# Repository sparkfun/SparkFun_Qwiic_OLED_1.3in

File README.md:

SparkFun Qwiic OLED 1.3in (128 x 64 white pixels)
========================================

[*Qwiic OLED 1.3in (128 x 64 white pixels) (LCD-23453)*](https://www.sparkfun.com/products/23453)

The SparkFun Qwiic OLED 1.3in (128 x 64 white pixels) Breakout is a Qwiic-enabled OLED display.

Repository Contents
-------------------

* **/Hardware** - Eagle design files (.brd, .sch)

Documentation
--------------
* **[Library](https://github.com/sparkfun/SparkFun_Qwiic_OLED_Arduino_Library)** - Latest Arduino library for the SparkFun Qwiic OLED 1.3in Breakout.
* **[Hookup Guide](https://docs.sparkfun.com/SparkFun_Qwiic_OLED_1.3in)** - Basic hookup guide for the SparkFun Qwiic OLED 1.3in

License Information
-------------------

This product is _**open source**_! 

Please review the LICENSE.md file for license information. 

If you have any questions or concerns on licensing, please contact techsupport@sparkfun.com.

Distributed as-is; no warranty is given.

- Your friends at SparkFun.

_<COLLABORATION CREDIT>_

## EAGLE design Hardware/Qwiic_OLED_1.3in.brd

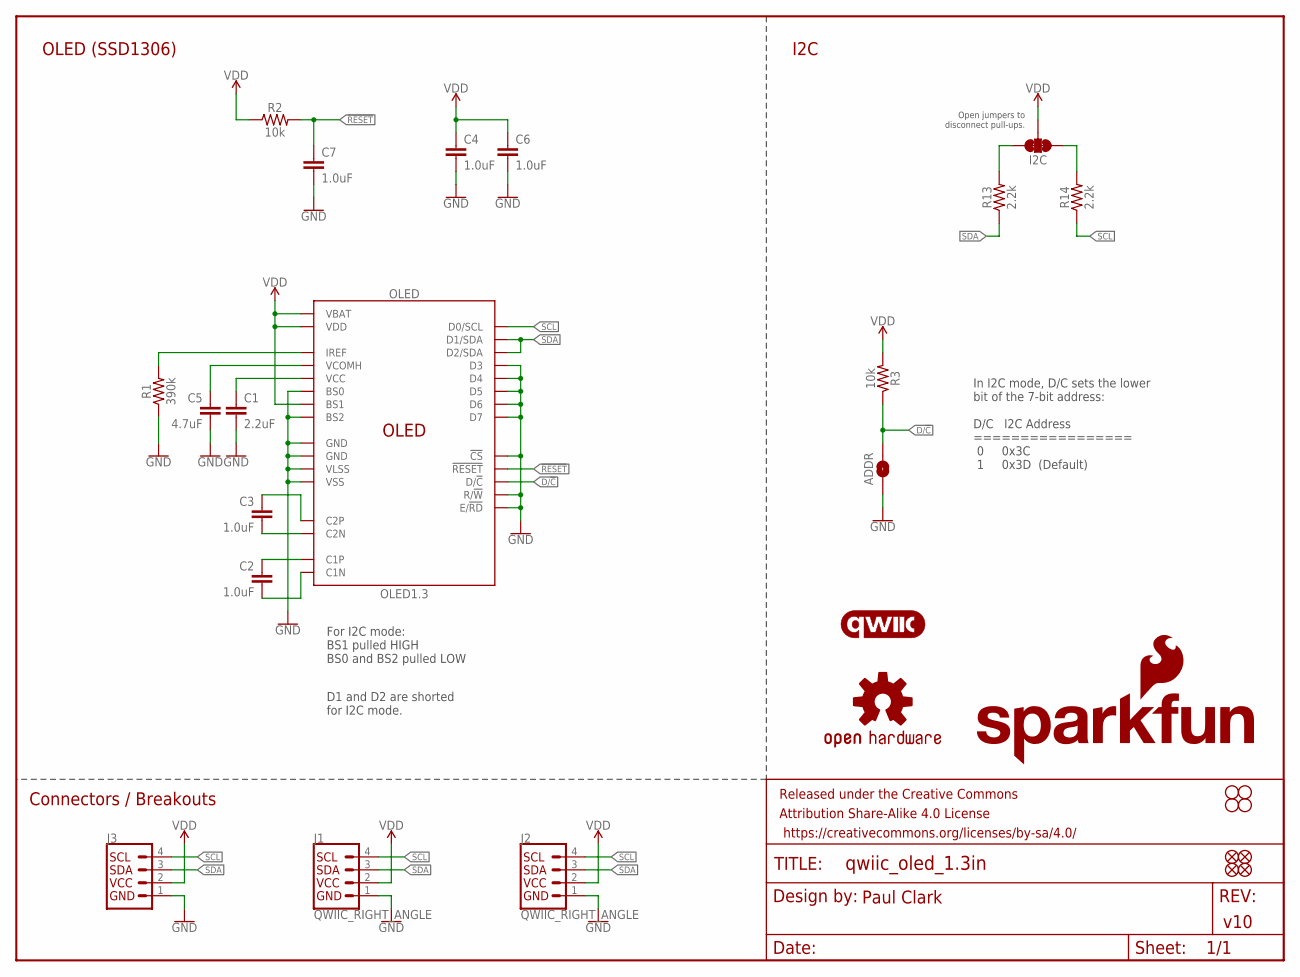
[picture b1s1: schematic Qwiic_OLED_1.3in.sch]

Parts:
ADDR: JUMPER-SMT_2_NO_SILK; SMT-JUMPER_2_NO_SILK
C1: 2.2uF; 0603
C2, C3, C4, C6, C7: 1.0uF; 0603
C5: 4.7uF; 0603
FID1, FID2, FID3, FID4: FIDUCIAL1X2; FIDUCIAL-1X2
FRAME1: FRAME-LETTER; CREATIVE_COMMONS
H1, H2, H3, H4: STAND-OFF
I2C: JUMPER-SMT_3_2-NC_TRACE_SILK; SMT-JUMPER_3_2-NC_TRACE_SILK
J1, J2: QWIIC_RIGHT_ANGLE; JST04_1MM_RA
J3: I2C_STANDARD_NO_SILK; 1X04_NO_SILK
LOGO1: QWIIC_LOGO_6MM; QWIIC_6MM
LOGO3: OSHW-LOGOS; OSHW-LOGO-S
LOGO4: SFE_LOGO_NAME_FLAME.1_INCH; SFE_LOGO_NAME_FLAME_.1
OLED: OLED1.3; OLED-1.3-128X64
R1: 390k; 0603
R2, R3: 10k; 0603
R13, R14: 2.2k; 0603

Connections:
!RESET!: C7.1, OLED.14 (!RESET!), R2.2
C1N: C2.2, OLED.5 (C1N)
C1P: C2.1, OLED.4 (C1P)
C2N: C3.2, OLED.3 (C2N)
C2P: C3.1, OLED.2 (C2P)
D/!C!: ADDR.2, OLED.15 (D/!C!), R3.1
GND: ADDR.1, C1.2, C4.2, C5.2, C6.2, C7.2, J1.1, J2.1, J3.1 (GND), OLED.1 (GND), OLED.8 (VSS), OLED.10 (BS0), OLED.12 (BS2), OLED.13 (!CS!), OLED.16 (R/!W!), OLED.17 (E/!RD!), OLED.21 (D3), OLED.22 (D4), OLED.23 (D5), OLED.24 (D6), OLED.25 (D7), OLED.29 (VLSS), OLED.30 (GND), R1.1
IREF: OLED.26 (IREF), R1.2
unnamed: I2C.3, R13.2
unnamed: I2C.1, R14.2
SCL: J1.4, J2.4, J3.4 (SCL), OLED.18 (D0/SCL), R14.1
SDA: J1.3, J2.3, J3.3 (SDA), OLED.19 (D1/SDA), OLED.20 (D2/SDA), R13.1
VCC: C1.1, OLED.28 (VCC)
VCOMH: C5.1, OLED.27 (VCOMH)
VDD: C4.1, C6.1, I2C.2, J1.2, J2.2, J3.2 (VCC), OLED.6 (VBAT), OLED.9 (VDD), OLED.11 (BS1), R2.1, R3.2

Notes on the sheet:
v10
D1 and D2 are shorted for I2C mode.
In I2C mode, D/C sets the lower bit of the 7-bit address: D/C I2C Address ================= 0 0x3C 1 0x3D (Default)
For I2C mode: BS1 pulled HIGH BS0 and BS2 pulled LOW
Open jumpers to disconnect pull-ups.
Paul Clark
OLED (SSD1306)
Connectors / Breakouts
I2C

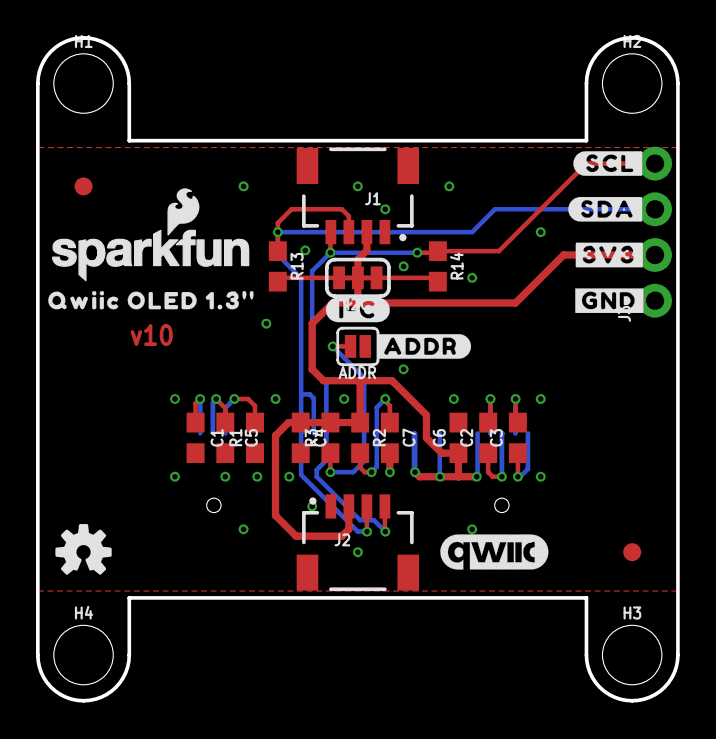
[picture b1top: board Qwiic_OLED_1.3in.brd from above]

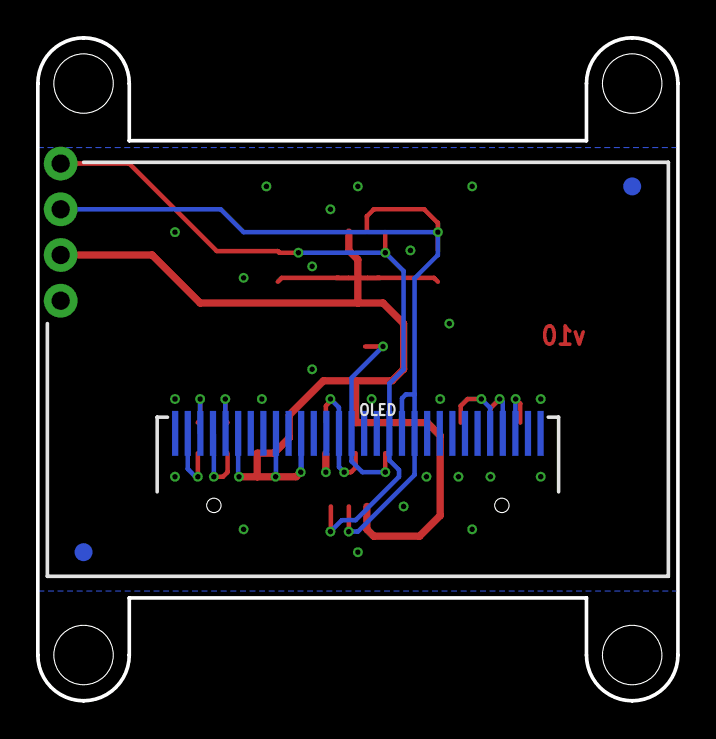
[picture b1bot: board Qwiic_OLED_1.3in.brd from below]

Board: 2 copper layers, 35.6 x 36.8 mm, 37 parts (3 on the bottom side), 15 nets.

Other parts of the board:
U$1: QWIIC_OLED_1#3##0
U$2: #I�C#2
U$3: #3V3#2
U$4: #ADDR#5
U$5: #GND#4
U$6: #SCL#0
U$7: #SDA#1

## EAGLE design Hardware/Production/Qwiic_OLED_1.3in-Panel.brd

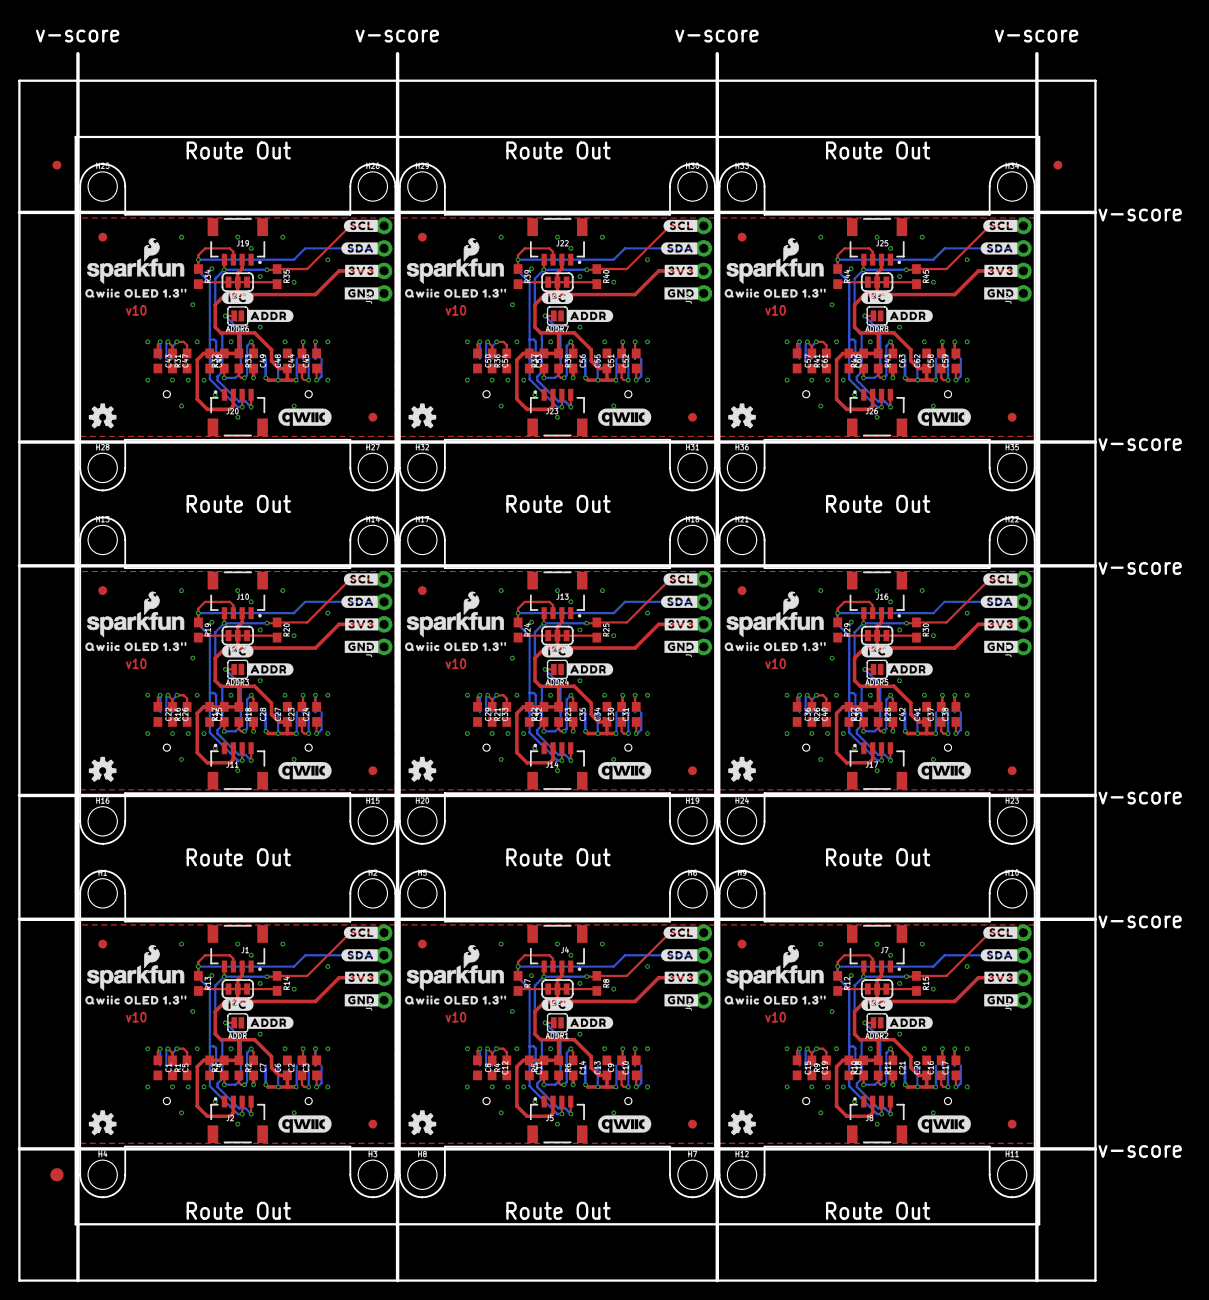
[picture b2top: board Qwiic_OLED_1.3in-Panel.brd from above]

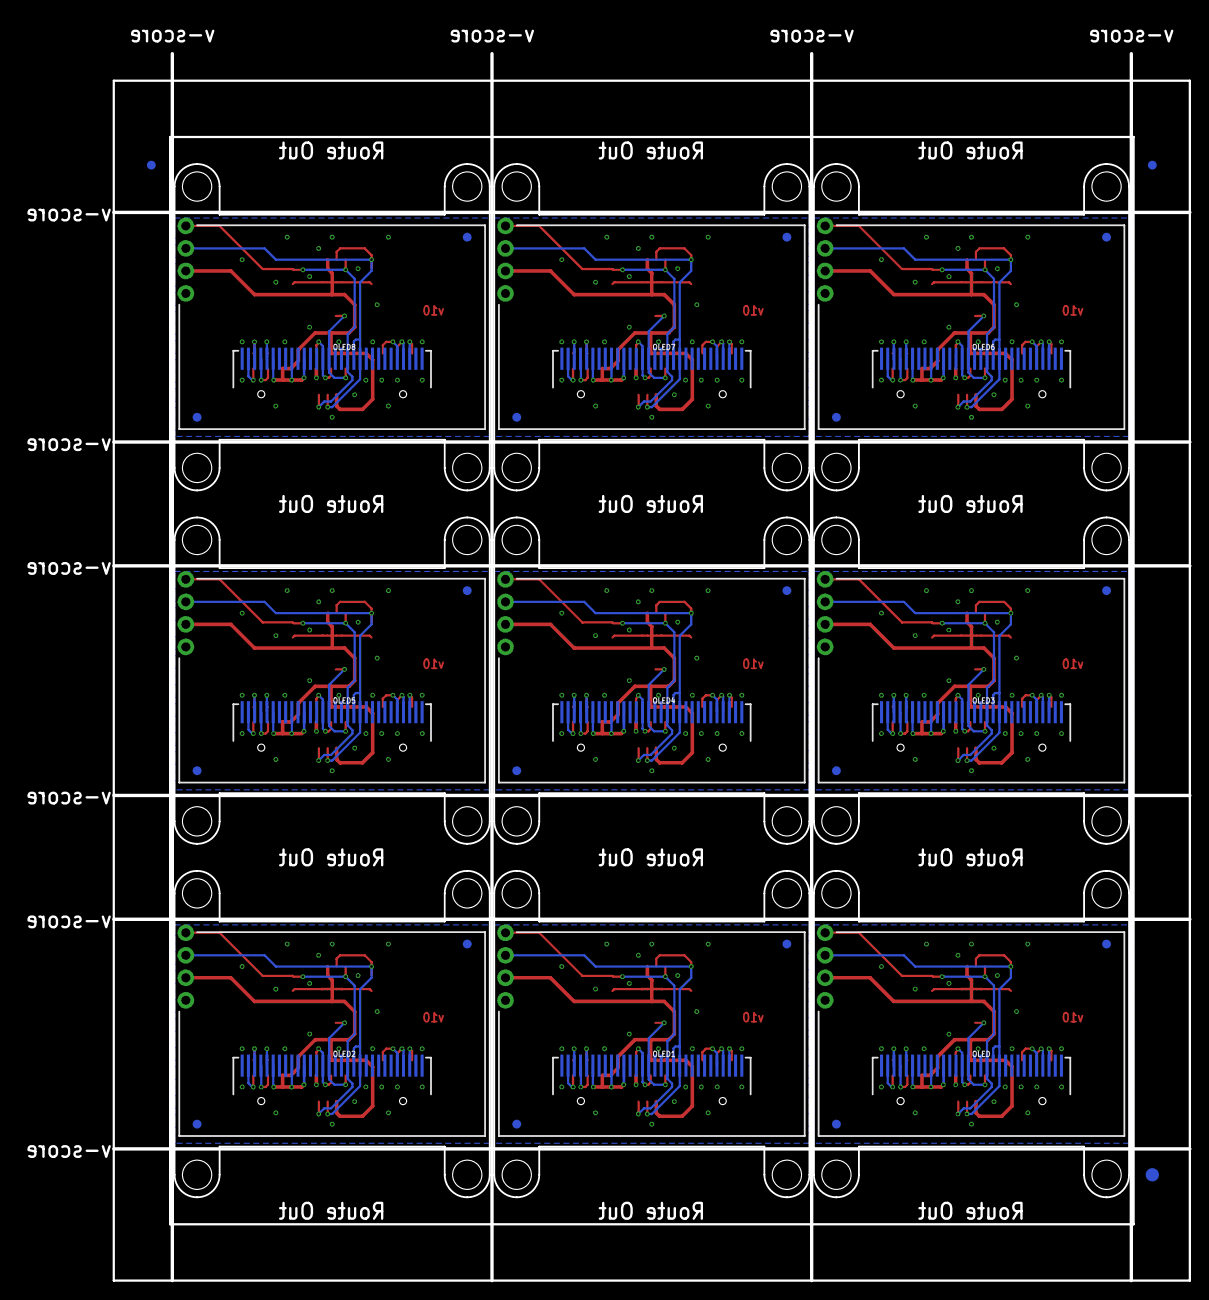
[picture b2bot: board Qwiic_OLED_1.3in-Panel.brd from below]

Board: 2 copper layers, 132.1 x 142.3 mm, 330 parts (30 on the bottom side), 135 nets.

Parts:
ADDR, ADDR1, ADDR2, ADDR3, ADDR4, ADDR5, ADDR6, ADDR7, ADDR8: JUMPER-SMT_2_NO_SILK; SMT-JUMPER_2_NO_SILK
C1, C8, C15, C22, C29, C36, C43, C50, C57: 2.2uF; 0603
C2, C3, C4, C6, C7, C9, C10, C11, C13, C14, C16, C17, C18, C20, C21, C23, C24, C25, C27, C28, C30, C31, C32, C34, C35, C37, C38, C39, C41, C42, C44, C45, C46, C48, C49, C51, C52, C53, C55, C56, C58, C59, C60, C62, C63: 1.0uF; 0603
C5, C12, C19, C26, C33, C40, C47, C54, C61: 4.7uF; 0603
E$1, E$2, E$3, E$4: FIDUCIAL-1X2
E$5, E$6: FIDUCIAL-1.5X3
FID1, FID2, FID3, FID4, FID5, FID6, FID7, FID8, FID9, FID10, FID11, FID12, FID13, FID14, FID15, FID16, FID17, FID18, FID19, FID20, FID21, FID22, FID23, FID24, FID25, FID26, FID27, FID28, FID29, FID30, FID31, FID32, FID33, FID34, FID35, FID36: FIDUCIAL1X2; FIDUCIAL-1X2
H1, H2, H3, H4, H5, H6, H7, H8, H9, H10, H11, H12, H13, H14, H15, H16, H17, H18, H19, H20, H21, H22, H23, H24, H25, H26, H27, H28, H29, H30, H31, H32, H33, H34, H35, H36: STAND-OFF
I2C, I2C1, I2C2, I2C3, I2C4, I2C5, I2C6, I2C7, I2C8: JUMPER-SMT_3_2-NC_TRACE_SILK; SMT-JUMPER_3_2-NC_TRACE_SILK
J1, J2, J4, J5, J7, J8, J10, J11, J13, J14, J16, J17, J19, J20, J22, J23, J25, J26: QWIIC_RIGHT_ANGLE; JST04_1MM_RA
J3, J6, J9, J12, J15, J18, J21, J24, J27: 1X04_NO_SILK
LOGO1, LOGO6, LOGO9, LOGO12, LOGO15, LOGO18, LOGO21, LOGO24, LOGO27: QWIIC_LOGO_6MM; QWIIC_6MM
LOGO2, LOGO3, LOGO7, LOGO10, LOGO13, LOGO16, LOGO19, LOGO22, LOGO25: OSHW-LOGOS; OSHW-LOGO-S
LOGO4, LOGO5, LOGO8, LOGO11, LOGO14, LOGO17, LOGO20, LOGO23, LOGO26: SFE_LOGO_NAME_FLAME.1_INCH; SFE_LOGO_NAME_FLAME_.1
OLED, OLED1, OLED2, OLED3, OLED4, OLED5, OLED6, OLED7, OLED8: OLED1.3; OLED-1.3-128X64
R1, R4, R9, R16, R21, R26, R31, R36, R41: 390k; 0603
R2, R3, R5, R6, R10, R11, R17, R18, R22, R23, R27, R28, R32, R33, R37, R38, R42, R43: 10k; 0603
R7, R8, R12, R13, R14, R15, R19, R20, R24, R25, R29, R30, R34, R35, R39, R40, R44, R45: 2.2k; 0603
U$1, U$8, U$15, U$22, U$29, U$36, U$43, U$50, U$57: QWIIC_OLED_1#3##0
U$2, U$9, U$16, U$23, U$30, U$37, U$44, U$51, U$58: #I�C#2
U$3, U$10, U$17, U$24, U$31, U$38, U$45, U$52, U$59: #3V3#2
U$4, U$11, U$18, U$25, U$32, U$39, U$46, U$53, U$60: #ADDR#5
U$5, U$12, U$19, U$26, U$33, U$40, U$47, U$54, U$61: #GND#4
U$6, U$13, U$20, U$27, U$34, U$41, U$48, U$55, U$62: #SCL#0
U$7, U$14, U$21, U$28, U$35, U$42, U$49, U$56, U$63: #SDA#1

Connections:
!RESET!: C7.1, OLED.14, R2.2
!RESET!1: C14.1, OLED1.14, R6.2
!RESET!2: C21.1, OLED2.14, R11.2
!RESET!3: C28.1, OLED3.14, R18.2
!RESET!4: C35.1, OLED4.14, R23.2
!RESET!5: C42.1, OLED5.14, R28.2
!RESET!6: C49.1, OLED6.14, R33.2
!RESET!7: C56.1, OLED7.14, R38.2
!RESET!8: C63.1, OLED8.14, R43.2
C1N: C2.2, OLED.5
C1N1: C9.2, OLED1.5
C1N2: C16.2, OLED2.5
C1N3: C23.2, OLED3.5
C1N4: C30.2, OLED4.5
C1N5: C37.2, OLED5.5
C1N6: C44.2, OLED6.5
C1N7: C51.2, OLED7.5
C1N8: C58.2, OLED8.5
C1P: C2.1, OLED.4
C1P1: C9.1, OLED1.4
C1P2: C16.1, OLED2.4
C1P3: C23.1, OLED3.4
C1P4: C30.1, OLED4.4
C1P5: C37.1, OLED5.4
C1P6: C44.1, OLED6.4
C1P7: C51.1, OLED7.4
C1P8: C58.1, OLED8.4
C2N: C3.2, OLED.3
C2N1: C10.2, OLED1.3
C2N2: C17.2, OLED2.3
C2N3: C24.2, OLED3.3
C2N4: C31.2, OLED4.3
C2N5: C38.2, OLED5.3
C2N6: C45.2, OLED6.3
C2N7: C52.2, OLED7.3
C2N8: C59.2, OLED8.3
C2P: C3.1, OLED.2
C2P1: C10.1, OLED1.2
C2P2: C17.1, OLED2.2
C2P3: C24.1, OLED3.2
C2P4: C31.1, OLED4.2
C2P5: C38.1, OLED5.2
C2P6: C45.1, OLED6.2
C2P7: C52.1, OLED7.2
C2P8: C59.1, OLED8.2
D/!C!: ADDR.2, OLED.15, R3.1
D/!C!1: ADDR1.2, OLED1.15, R5.1
D/!C!2: ADDR2.2, OLED2.15, R10.1
D/!C!3: ADDR3.2, OLED3.15, R17.1
D/!C!4: ADDR4.2, OLED4.15, R22.1
D/!C!5: ADDR5.2, OLED5.15, R27.1
D/!C!6: ADDR6.2, OLED6.15, R32.1
D/!C!7: ADDR7.2, OLED7.15, R37.1
D/!C!8: ADDR8.2, OLED8.15, R42.1
GND: ADDR.1, C1.2, C4.2, C5.2, C6.2, C7.2, J1.1, J2.1, J3.1, OLED.1, OLED.8, OLED.10, OLED.12, OLED.13, OLED.16, OLED.17, OLED.21, OLED.22, OLED.23, OLED.24, OLED.25, OLED.29, OLED.30, R1.1
GND1: ADDR1.1, C8.2, C11.2, C12.2, C13.2, C14.2, J4.1, J5.1, J6.1, OLED1.1, OLED1.8, OLED1.10, OLED1.12, OLED1.13, OLED1.16, OLED1.17, OLED1.21, OLED1.22, OLED1.23, OLED1.24, OLED1.25, OLED1.29, OLED1.30, R4.1
GND2: ADDR2.1, C15.2, C18.2, C19.2, C20.2, C21.2, J7.1, J8.1, J9.1, OLED2.1, OLED2.8, OLED2.10, OLED2.12, OLED2.13, OLED2.16, OLED2.17, OLED2.21, OLED2.22, OLED2.23, OLED2.24, OLED2.25, OLED2.29, OLED2.30, R9.1
GND3: ADDR3.1, C22.2, C25.2, C26.2, C27.2, C28.2, J10.1, J11.1, J12.1, OLED3.1, OLED3.8, OLED3.10, OLED3.12, OLED3.13, OLED3.16, OLED3.17, OLED3.21, OLED3.22, OLED3.23, OLED3.24, OLED3.25, OLED3.29, OLED3.30, R16.1
GND4: ADDR4.1, C29.2, C32.2, C33.2, C34.2, C35.2, J13.1, J14.1, J15.1, OLED4.1, OLED4.8, OLED4.10, OLED4.12, OLED4.13, OLED4.16, OLED4.17, OLED4.21, OLED4.22, OLED4.23, OLED4.24, OLED4.25, OLED4.29, OLED4.30, R21.1
GND5: ADDR5.1, C36.2, C39.2, C40.2, C41.2, C42.2, J16.1, J17.1, J18.1, OLED5.1, OLED5.8, OLED5.10, OLED5.12, OLED5.13, OLED5.16, OLED5.17, OLED5.21, OLED5.22, OLED5.23, OLED5.24, OLED5.25, OLED5.29, OLED5.30, R26.1
GND6: ADDR6.1, C43.2, C46.2, C47.2, C48.2, C49.2, J19.1, J20.1, J21.1, OLED6.1, OLED6.8, OLED6.10, OLED6.12, OLED6.13, OLED6.16, OLED6.17, OLED6.21, OLED6.22, OLED6.23, OLED6.24, OLED6.25, OLED6.29, OLED6.30, R31.1
GND7: ADDR7.1, C50.2, C53.2, C54.2, C55.2, C56.2, J22.1, J23.1, J24.1, OLED7.1, OLED7.8, OLED7.10, OLED7.12, OLED7.13, OLED7.16, OLED7.17, OLED7.21, OLED7.22, OLED7.23, OLED7.24, OLED7.25, OLED7.29, OLED7.30, R36.1
GND8: ADDR8.1, C57.2, C60.2, C61.2, C62.2, C63.2, J25.1, J26.1, J27.1, OLED8.1, OLED8.8, OLED8.10, OLED8.12, OLED8.13, OLED8.16, OLED8.17, OLED8.21, OLED8.22, OLED8.23, OLED8.24, OLED8.25, OLED8.29, OLED8.30, R41.1
IREF: OLED.26, R1.2
IREF1: OLED1.26, R4.2
IREF2: OLED2.26, R9.2
IREF3: OLED3.26, R16.2
IREF4: OLED4.26, R21.2
IREF5: OLED5.26, R26.2
IREF6: OLED6.26, R31.2
IREF7: OLED7.26, R36.2
IREF8: OLED8.26, R41.2
unnamed: I2C1.3, R7.2
unnamed: I2C1.1, R8.2
unnamed: I2C2.3, R12.2
unnamed: I2C.3, R13.2
unnamed: I2C.1, R14.2
unnamed: I2C2.1, R15.2
unnamed: I2C3.3, R19.2
unnamed: I2C3.1, R20.2
unnamed: I2C4.3, R24.2
unnamed: I2C4.1, R25.2
unnamed: I2C5.3, R29.2
unnamed: I2C5.1, R30.2
unnamed: I2C6.3, R34.2
unnamed: I2C6.1, R35.2
unnamed: I2C7.3, R39.2
unnamed: I2C7.1, R40.2
unnamed: I2C8.3, R44.2
unnamed: I2C8.1, R45.2
SCL: J1.4, J2.4, J3.4, OLED.18, R14.1
SCL1: J4.4, J5.4, J6.4, OLED1.18, R8.1
SCL2: J7.4, J8.4, J9.4, OLED2.18, R15.1
SCL3: J10.4, J11.4, J12.4, OLED3.18, R20.1
SCL4: J13.4, J14.4, J15.4, OLED4.18, R25.1
SCL5: J16.4, J17.4, J18.4, OLED5.18, R30.1
SCL6: J19.4, J20.4, J21.4, OLED6.18, R35.1
SCL7: J22.4, J23.4, J24.4, OLED7.18, R40.1
SCL8: J25.4, J26.4, J27.4, OLED8.18, R45.1
SDA: J1.3, J2.3, J3.3, OLED.19, OLED.20, R13.1
SDA1: J4.3, J5.3, J6.3, OLED1.19, OLED1.20, R7.1
SDA2: J7.3, J8.3, J9.3, OLED2.19, OLED2.20, R12.1
SDA3: J10.3, J11.3, J12.3, OLED3.19, OLED3.20, R19.1
SDA4: J13.3, J14.3, J15.3, OLED4.19, OLED4.20, R24.1
SDA5: J16.3, J17.3, J18.3, OLED5.19, OLED5.20, R29.1
SDA6: J19.3, J20.3, J21.3, OLED6.19, OLED6.20, R34.1
SDA7: J22.3, J23.3, J24.3, OLED7.19, OLED7.20, R39.1
SDA8: J25.3, J26.3, J27.3, OLED8.19, OLED8.20, R44.1
VCC: C1.1, OLED.28
VCC1: C8.1, OLED1.28
VCC2: C15.1, OLED2.28
VCC3: C22.1, OLED3.28
VCC4: C29.1, OLED4.28
VCC5: C36.1, OLED5.28
VCC6: C43.1, OLED6.28
VCC7: C50.1, OLED7.28
VCC8: C57.1, OLED8.28
VCOMH: C5.1, OLED.27
VCOMH1: C12.1, OLED1.27
VCOMH2: C19.1, OLED2.27
VCOMH3: C26.1, OLED3.27
VCOMH4: C33.1, OLED4.27
VCOMH5: C40.1, OLED5.27
VCOMH6: C47.1, OLED6.27
VCOMH7: C54.1, OLED7.27
VCOMH8: C61.1, OLED8.27
VDD: C4.1, C6.1, I2C.2, J1.2, J2.2, J3.2, OLED.6, OLED.9, OLED.11, R2.1, R3.2
VDD1: C11.1, C13.1, I2C1.2, J4.2, J5.2, J6.2, OLED1.6, OLED1.9, OLED1.11, R5.2, R6.1
VDD2: C18.1, C20.1, I2C2.2, J7.2, J8.2, J9.2, OLED2.6, OLED2.9, OLED2.11, R10.2, R11.1
VDD3: C25.1, C27.1, I2C3.2, J10.2, J11.2, J12.2, OLED3.6, OLED3.9, OLED3.11, R17.2, R18.1
VDD4: C32.1, C34.1, I2C4.2, J13.2, J14.2, J15.2, OLED4.6, OLED4.9, OLED4.11, R22.2, R23.1
VDD5: C39.1, C41.1, I2C5.2, J16.2, J17.2, J18.2, OLED5.6, OLED5.9, OLED5.11, R27.2, R28.1
VDD6: C46.1, C48.1, I2C6.2, J19.2, J20.2, J21.2, OLED6.6, OLED6.9, OLED6.11, R32.2, R33.1
VDD7: C53.1, C55.1, I2C7.2, J22.2, J23.2, J24.2, OLED7.6, OLED7.9, OLED7.11, R37.2, R38.1
VDD8: C60.1, C62.1, I2C8.2, J25.2, J26.2, J27.2, OLED8.6, OLED8.9, OLED8.11, R42.2, R43.1

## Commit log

2023-09-05 Panelized
2023-09-06 Connect CS to GND
2023-11-02 Initial pass of docs
2023-11-02 Updates to Hardware Overview
2023-11-02 Update images and reqd mats list
2023-11-02 Fix bold formatting
2023-11-02 Adding screen image to overview
2023-11-03 Adding examples page and updating images and overviews
2023-11-03 Fixing links for single page view
2023-11-06 Updating Links to GitHub and single page list
2023-11-06 Updating introduction
2023-11-07 Adding example
2023-11-07 Updating Resources
2023-11-29 Updates for examples and single page
2023-11-29 Updating Repo name throughout the doc
2023-11-30 Updates per Paul
2023-11-30 Fixing name of Eagle File zip
2023-11-30 Update resources links
2023-12-01 Adding target to open in new page
2023-12-01 Fixing doc link
2023-12-01 Deployed a5116a5 with MkDocs version: 1.5.3
2024-05-20 Updating Datasheet per customer
2024-05-20 Deployed 402a094 with MkDocs version: 1.6.0
2025-09-11 Remove git-authors
2026-06-03 Deployed fe1cef1 with MkDocs version: 1.6.1

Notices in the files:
parts and their libraries:
SparkFun-Aesthetics: Licensing: Creative Commons ShareAlike 4.0 International - https://creativecommons.org/licenses/by-sa/4.0
SparkFun-Aesthetics: Released under the Creative Commons Attribution Share-Alike 4.0 License
SparkFun-Aesthetics: https://creativecommons.org/licenses/by-sa/4.0
